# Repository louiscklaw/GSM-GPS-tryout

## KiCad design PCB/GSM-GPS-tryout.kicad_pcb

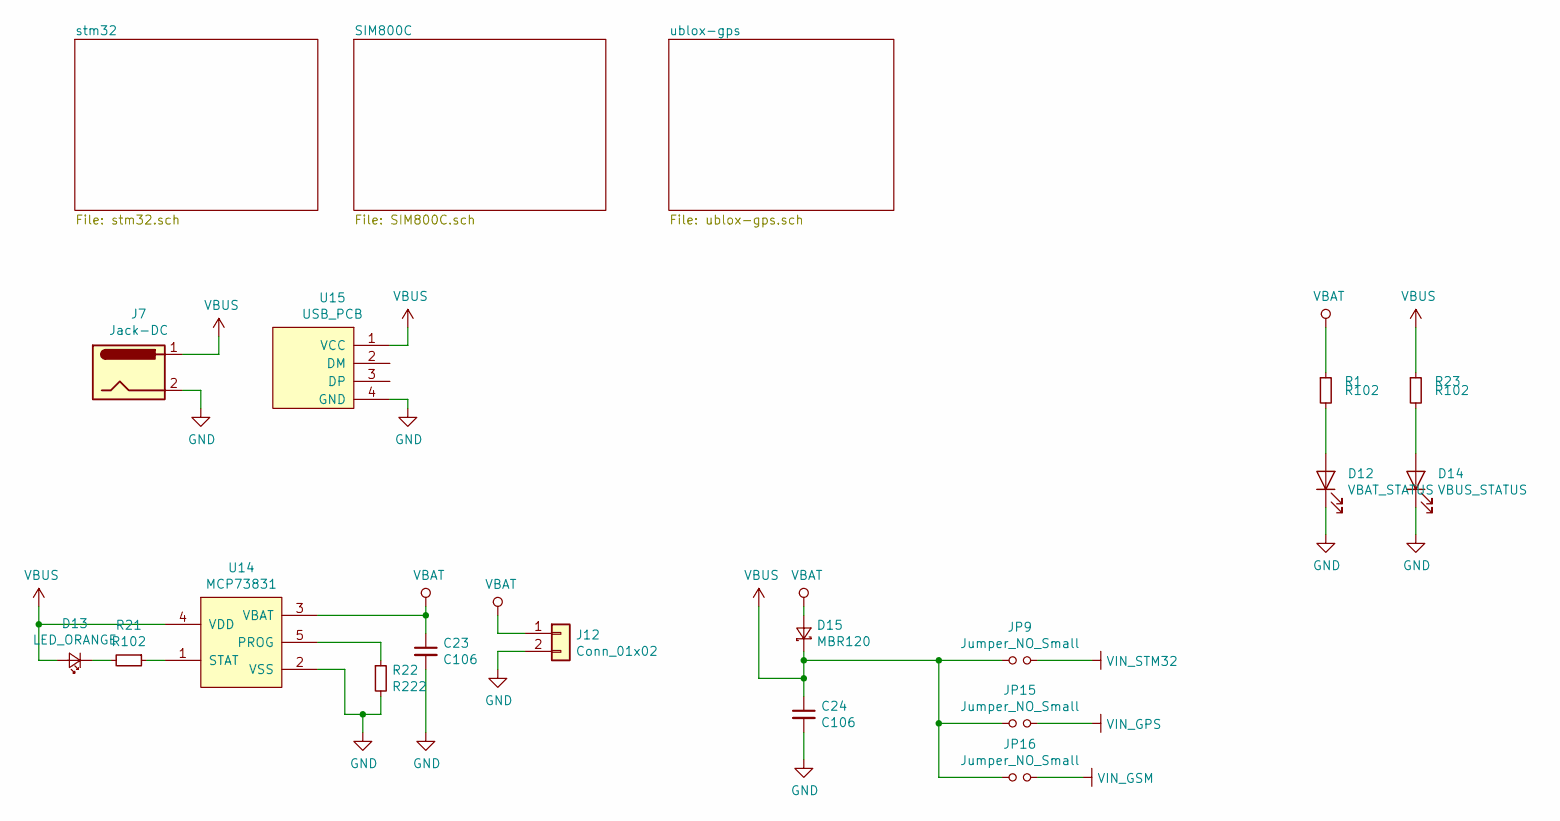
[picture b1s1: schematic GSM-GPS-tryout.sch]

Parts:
C23, C24: C106; C_0805_2012Metric_Pad1.15x1.40mm_HandSolder
D12: VBAT_STATUS; LED_0805_2012Metric_Pad1.15x1.40mm_HandSolder
D13: LED_ORANGE; LED_0805_2012Metric_Castellated
D14: VBUS_STATUS; LED_0805_2012Metric_Pad1.15x1.40mm_HandSolder
D15: MBR120; D_SOD-123F
J7: Jack-DC; CUI-PJ-102A_dc-barrel-jack
J12: Conn_01x02; PinHeader_1x02_P2.54mm_Vertical
JP9, JP15, JP16: Jumper_NO_Small; SolderJumper-2_P1.3mm_Open_TrianglePad1.0x1.5mm
R1, R21, R23: R102; R_0805_2012Metric_Pad1.15x1.40mm_HandSolder
R22: R222; R_0805_2012Metric_Pad1.15x1.40mm_HandSolder
U14: MCP73831; SOT-23-5_HandSoldering
U15: USB_PCB; usb-PCB

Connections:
GND: C23.2, C24.2, D12.1 (K), D14.1 (K), J7.2, J12.2, R22.2, U14.2 (VSS), U15.4 (GND); also elsewhere on the board
unnamed: D12.2 (A), R1.2
unnamed: D13.1 (K), R21.2
unnamed: D14.2 (A), R23.2
unnamed: R21.1, U14.1 (STAT)
unnamed: R22.1, U14.5 (PROG)
VBAT: C23.1, D15.2 (A), J12.1, R1.1, U14.3 (VBAT)
VBUS: C24.1, D13.2 (A), D15.1 (K), J7.1, JP9.1, JP15.1, JP16.1, R23.1, U14.4 (VDD), U15.1 (VCC)
VIN_GPS: JP15.2; also elsewhere on the board
VIN_GSM: JP16.2; also elsewhere on the board
VIN_STM32: JP9.2; also elsewhere on the board

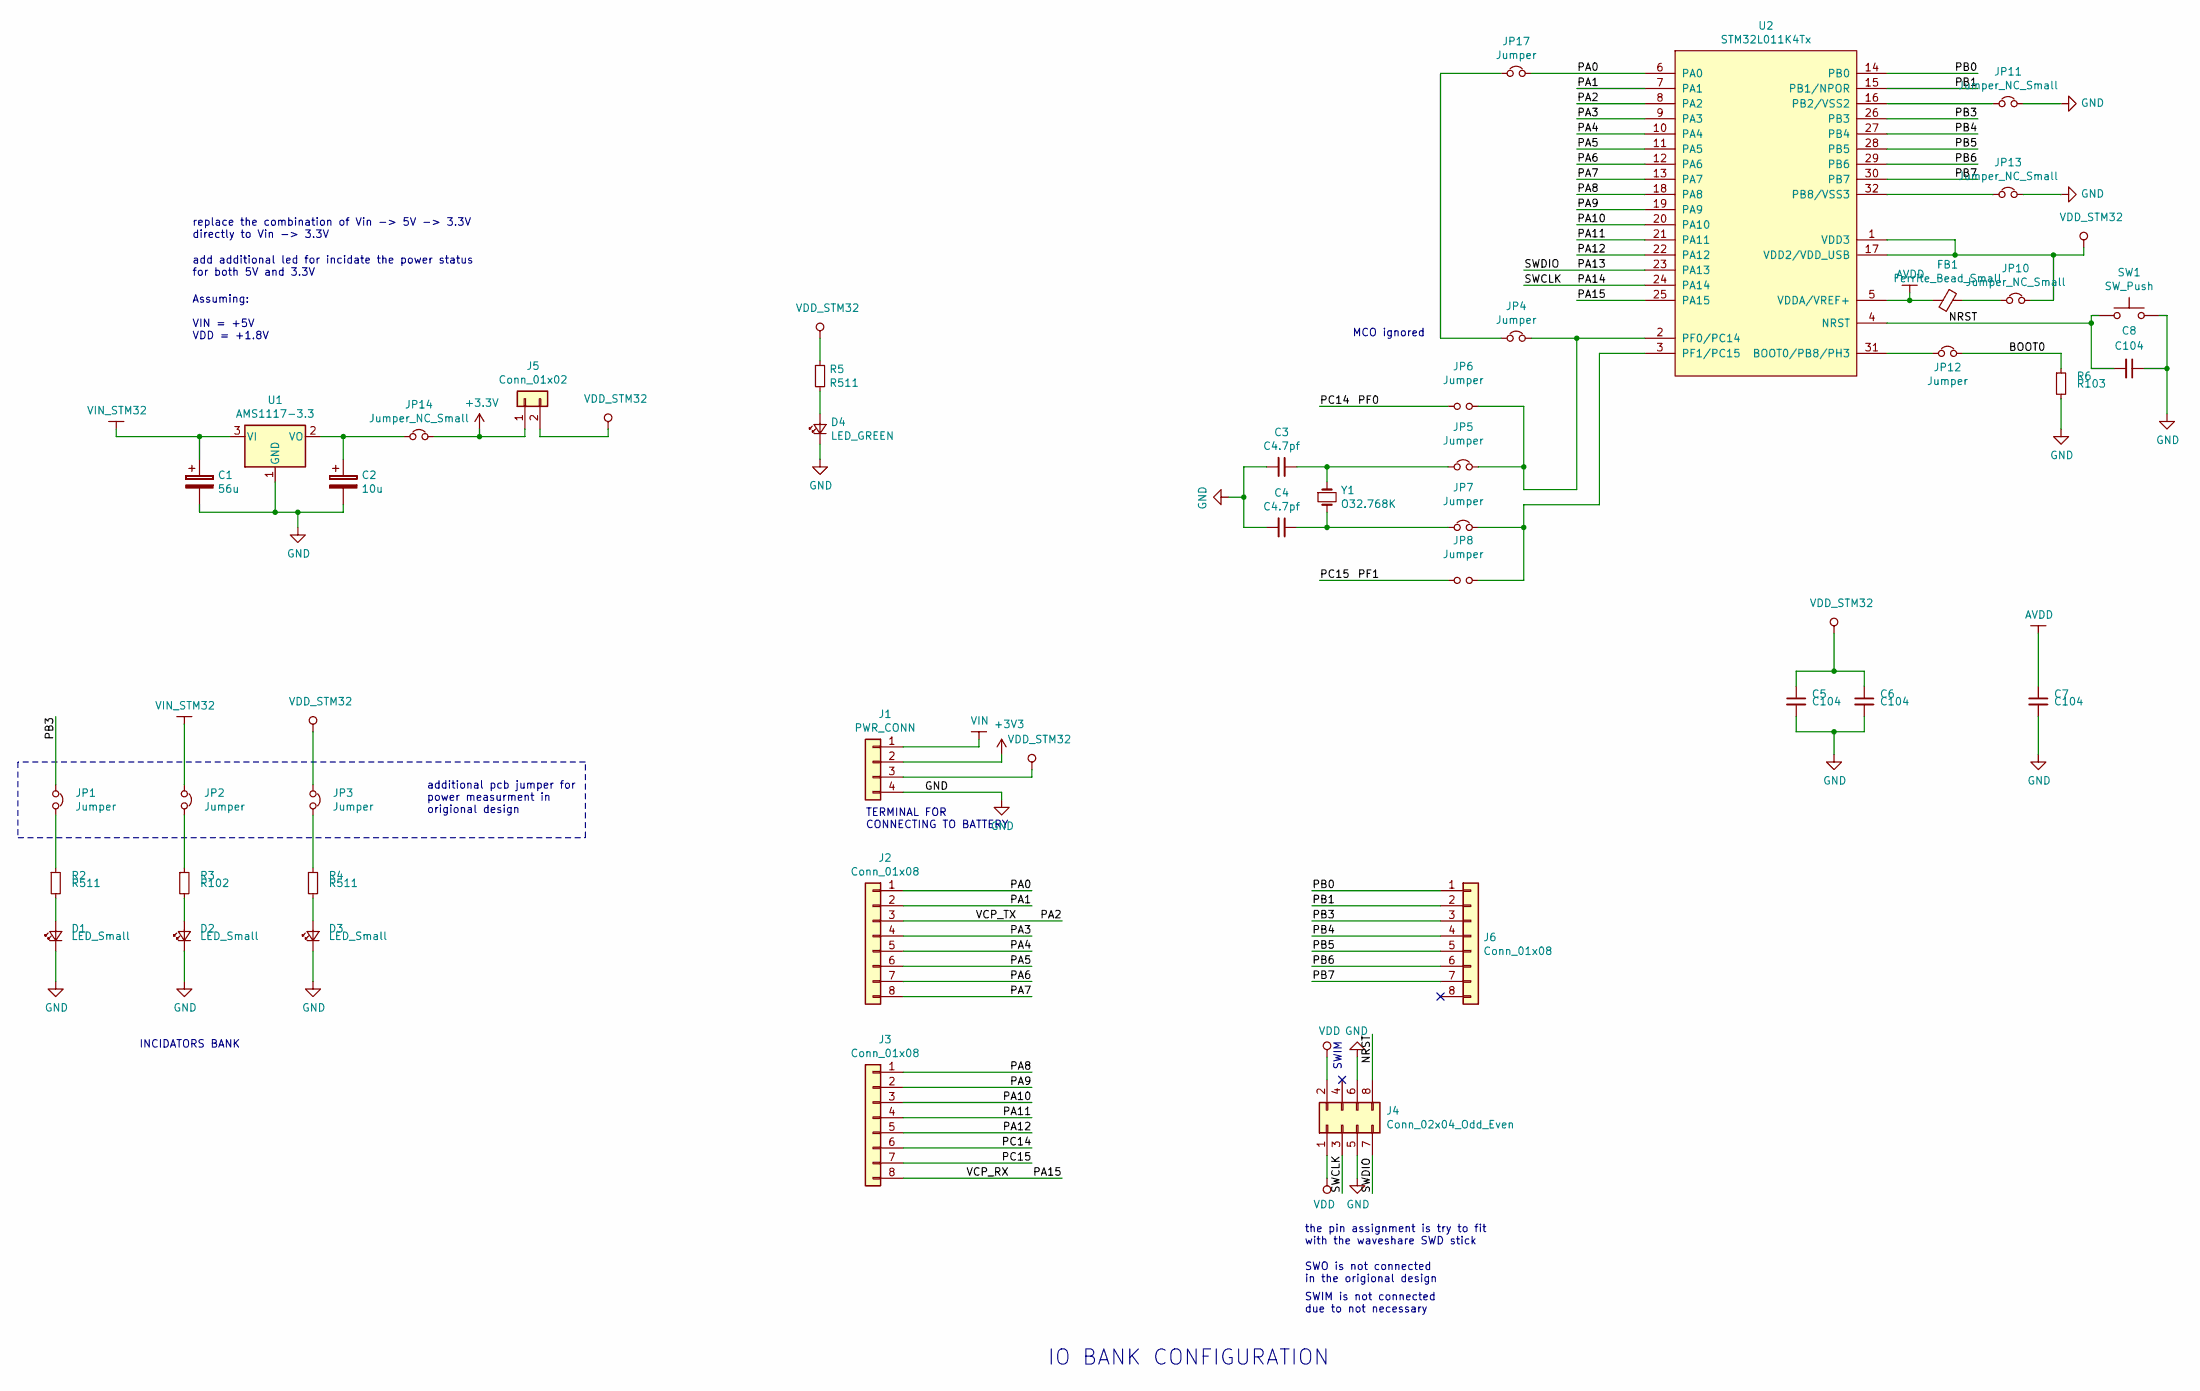
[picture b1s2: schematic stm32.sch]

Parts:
C1: 56u; CP_Elec_3x5.4
C2: 10u; CP_Elec_3x5.4
C3, C4: C4.7pf; C_0805_2012Metric_Pad1.15x1.40mm_HandSolder
C5, C6, C7, C8: C104; C_0805_2012Metric_Pad1.15x1.40mm_HandSolder
D1, D2, D3: LED_Small; LED_0805_2012Metric_Castellated
D4: LED_GREEN; LED_0805_2012Metric_Castellated
FB1: Ferrite_Bead_Small; inductor_smd_0805
J1: PWR_CONN; PinHeader_1x04_P2.54mm_Vertical
J2, J3, J6: Conn_01x08; PinHeader_1x08_P2.54mm_Vertical
J4: Conn_02x04_Odd_Even; PinHeader_2x04_P2.54mm_Vertical
J5: Conn_01x02; PinHeader_1x02_P2.54mm_Vertical
JP1, JP2, JP3, JP4, JP5, JP7, JP12, JP17: Jumper; SolderJumper-2_P1.3mm_Bridged_Pad1.0x1.5mm
JP6, JP8: Jumper; SolderJumper-2_P1.3mm_Open_TrianglePad1.0x1.5mm
JP10, JP11, JP13, JP14: Jumper_NC_Small; SolderJumper-2_P1.3mm_Bridged_Pad1.0x1.5mm
R2, R4, R5: R511; R_0805_2012Metric_Pad1.15x1.40mm_HandSolder
R3: R102; R_0805_2012Metric_Pad1.15x1.40mm_HandSolder
R6: R103; R_0805_2012Metric_Pad1.15x1.40mm_HandSolder
SW1: SW_Push; PCB_PUSH
U1: AMS1117-3.3; SOT-223-3_TabPin2
U2: STM32L011K4Tx; LQFP-32_7x7mm_P0.8mm
Y1: O32.768K; Crystal_C38-LF_D3.0mm_L8.0mm_Vertical

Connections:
/stm32/BOOT0: JP12.2, R6.1
/stm32/NRST: C8.2, J4.8, SW1.1, U2.4 (NRST)
/stm32/PA0: J2.1, JP17.2, U2.6 (PA0)
/stm32/PA1: J2.2, U2.7 (PA1)
/stm32/PA2: J2.3, U2.8 (PA2)
/stm32/PA3: J2.4, U2.9 (PA3)
/stm32/PA4: J2.5, U2.10 (PA4)
/stm32/PA5: J2.6, U2.11 (PA5)
/stm32/PA6: J2.7, U2.12 (PA6)
/stm32/PA7: J2.8, U2.13 (PA7)
/stm32/PA8: J3.1, U2.18 (PA8)
/stm32/PA9: J3.2, U2.19 (PA9)
/stm32/PA10: J3.3, U2.20 (PA10)
/stm32/PA11: J3.4, U2.21 (PA11)
/stm32/PA12: J3.5, U2.22 (PA12)
/stm32/PA13: J4.7, U2.23 (PA13)
/stm32/PA14: J4.3, U2.24 (PA14)
/stm32/PA15: J3.8, U2.25 (PA15)
/stm32/PB0: J6.1, U2.14 (PB0)
/stm32/PB1: J6.2, U2.15 (PB1/NPOR)
/stm32/PB3: J6.3, JP1.1, U2.26 (PB3)
/stm32/PB4: J6.4, U2.27 (PB4)
/stm32/PB5: J6.5, U2.28 (PB5)
/stm32/PB6: J6.6, U2.29 (PB6)
/stm32/PB7: J6.7, U2.30 (PB7)
/stm32/PC14: J3.6, JP6.1
/stm32/PC15: J3.7, JP8.1
AVDD: C7.1, FB1.2, U2.5 (VDDA/VREF+)
GND: C1.2, C2.2, C3.2, C4.2, C5.2, C6.2, C7.2, C8.1, D1.1 (K), D2.1 (K), D3.1 (K), D4.1 (K), J1.4, J4.5, J4.6, JP11.2, JP13.2, R6.2, SW1.2, U1.1 (GND); also elsewhere on the board
unnamed: C2.1, JP14.1, U1.2 (VO)
unnamed: C3.1, JP5.1, Y1.1
unnamed: C4.1, JP7.1, Y1.2
unnamed: D1.2 (A), R2.2
unnamed: D2.2 (A), R3.2
unnamed: D3.2 (A), R4.2
unnamed: D4.2 (A), R5.2
unnamed: FB1.1, JP10.1
unnamed: JP1.2, R2.1
unnamed: JP2.2, R3.1
unnamed: JP3.2, R4.1
unnamed: JP4.2, JP5.2, JP6.2, U2.2 (PF0/PC14)
unnamed: JP7.2, JP8.2, U2.3 (PF1/PC15)
unnamed: JP11.1, U2.16 (PB2/VSS2)
unnamed: JP12.1, U2.31 (BOOT0/PB8/PH3)
unnamed: JP13.1, U2.32 (PB8/VSS3)
unnamed: JP4.1, JP17.1
VDD: J4.1, J4.2
VDD_STM32: C5.1, C6.1, J1.3, J5.2, JP3.1, JP10.2, R5.1, U2.1 (VDD3), U2.17 (VDD2/VDD_USB)
VIN: J1.1
VIN_STM32: C1.1, JP2.1, U1.3 (VI); also elsewhere on the board

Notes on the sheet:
replace the combination of Vin -> 5V -> 3.3V directly to Vin -> 3.3V
IO BANK CONFIGURATION
add additional led for incidate the power status for both 5V and 3.3V
INCIDATORS BANK
SWO is not connected in the origional design
the pin assignment is try to fit with the waveshare SWD stick
additional pcb jumper for power measurment in origional design
TERMINAL FOR CONNECTING TO BATTERY
SWIM is not connected due to not necessary
SWIM
MCO ignored
Assuming: VIN = +5V VDD = +1.8V

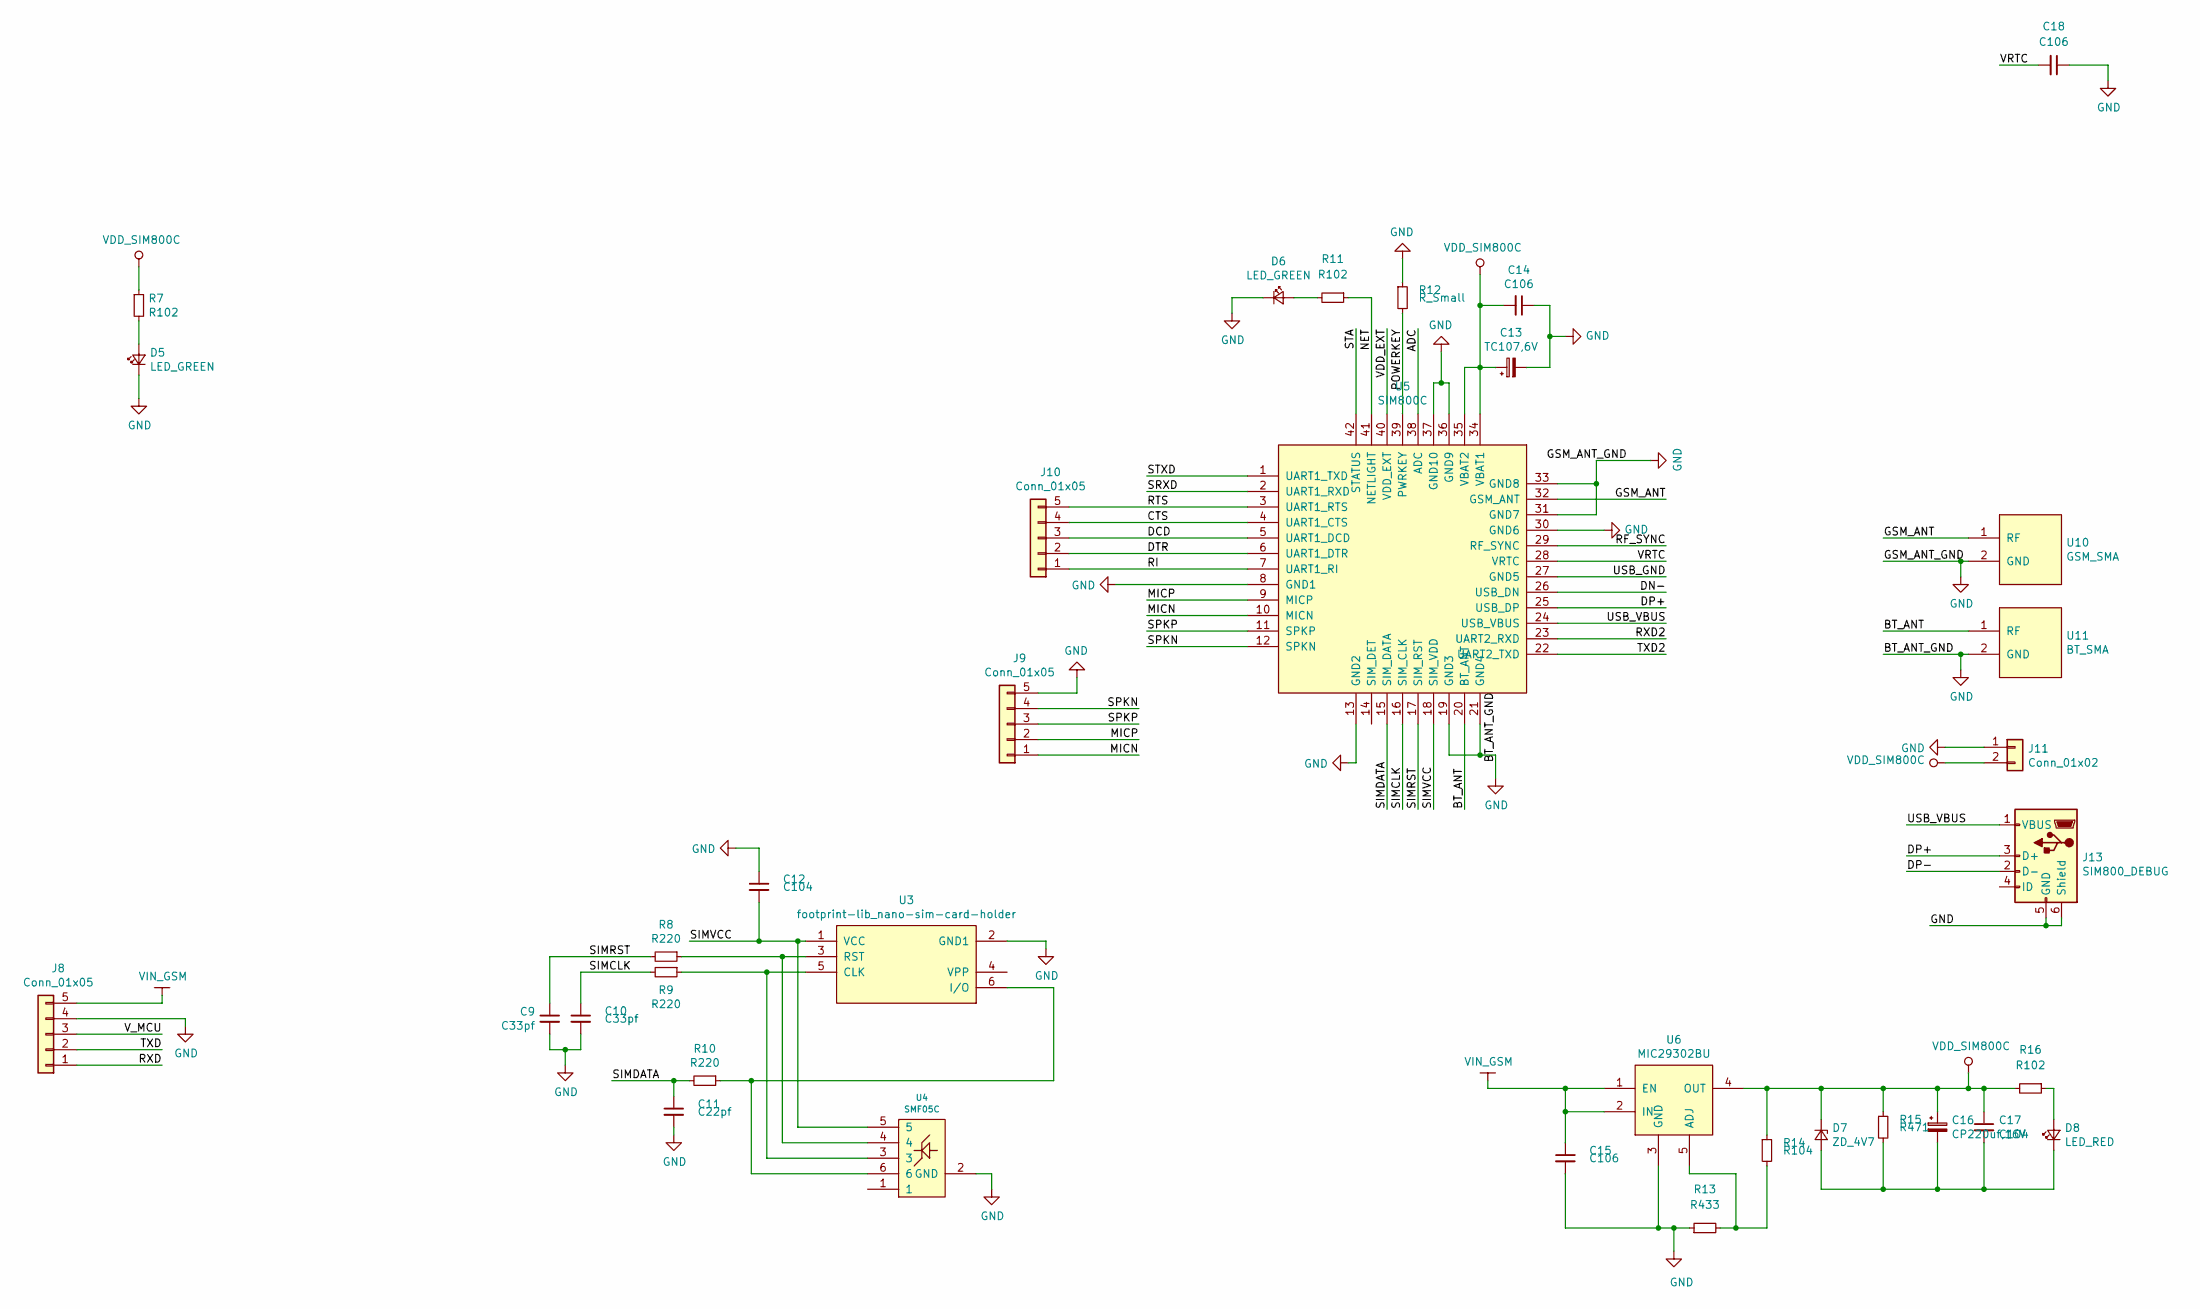
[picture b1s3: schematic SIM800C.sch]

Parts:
C9, C10: C33pf; C_0805_2012Metric_Pad1.15x1.40mm_HandSolder
C11: C22pf; C_0805_2012Metric_Pad1.15x1.40mm_HandSolder
C12: C104; C_0805_2012Metric_Pad1.15x1.40mm_HandSolder
C13: TC107,6V; CP_EIA-3216-12_Kemet-S_Pad1.58x1.35mm_HandSolder
C14, C15: C106; C_0805_2012Metric_Pad1.15x1.40mm_HandSolder
C16: CP220uf,16V; CP_Elec_6.3x7.7
C17: C104; C_0603_1608Metric_Pad1.05x0.95mm_HandSolder
C18: C106; C_0603_1608Metric_Pad1.05x0.95mm_HandSolder
D5, D6: LED_GREEN; LED_0805_2012Metric_Castellated
D7: ZD_4V7; D_1206_3216Metric_Pad1.42x1.75mm_HandSolder
D8: LED_RED; LED_0805_2012Metric_Castellated
J8, J9, J10: Conn_01x05; PinHeader_1x05_P2.54mm_Vertical
J11: Conn_01x02; PinHeader_1x02_P2.54mm_Vertical
J13: SIM800_DEBUG; conn_usb_B_micro_smd
R7, R11, R16: R102; R_0805_2012Metric_Pad1.15x1.40mm_HandSolder
R8, R9, R10: R220; R_0805_2012Metric_Pad1.15x1.40mm_HandSolder
R12: R_Small; R_0805_2012Metric_Pad1.15x1.40mm_HandSolder
R13: R433; R_0805_2012Metric_Pad1.15x1.40mm_HandSolder
R14: R104; R_0805_2012Metric_Pad1.15x1.40mm_HandSolder
R15: R471; R_0805_2012Metric_Pad1.15x1.40mm_HandSolder
U3: footprint-lib_nano-sim-card-holder; nano-sim-card-holder
U4: SMF05C; SOT-363_SC-70-6_Handsoldering
U5: SIM800C; LCC110P1570X1760X250-42N
U6: MIC29302BU; TO-263-5_TabPin3
U10: GSM_SMA; sma_straight_32k101-400l5
U11: BT_SMA; sma_straight_32k101-400l5

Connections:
/SIM800C/ADC: U5.38 (ADC)
/SIM800C/BT_ANT: U5.20 (BT_ANT), U11.1 (RF)
/SIM800C/CTS: J10.4, U5.4 (UART1_CTS)
/SIM800C/DCD: J10.3, U5.5 (UART1_DCD)
/SIM800C/DN-: U5.26 (USB_DN)
/SIM800C/DP+: J13.3 (D+), U5.25 (USB_DP)
/SIM800C/DP-: J13.2 (D-)
/SIM800C/DTR: J10.2, U5.6 (UART1_DTR)
/SIM800C/GSM_ANT: U5.32 (GSM_ANT), U10.1 (RF)
/SIM800C/MICN: J9.1, U5.10 (MICN)
/SIM800C/MICP: J9.2, U5.9 (MICP)
/SIM800C/NET: R11.1, U5.41 (NETLIGHT)
/SIM800C/POWERKEY: R12.2, U5.39 (PWRKEY)
/SIM800C/RF_SYNC: U5.29 (RF_SYNC)
/SIM800C/RI: J10.1, U5.7 (UART1_RI)
/SIM800C/RTS: J10.5, U5.3 (UART1_RTS)
/SIM800C/RXD: J8.1
/SIM800C/RXD2: U5.23 (UART2_RXD)
/SIM800C/SIMCLK: C10.1, R9.2, U5.16 (SIM_CLK)
/SIM800C/SIMDATA: C11.1, R10.2, U5.15 (SIM_DATA)
/SIM800C/SIMRST: C9.1, R8.2, U5.17 (SIM_RST)
/SIM800C/SIMVCC: C12.2, U3.1 (VCC), U4.5, U5.18 (SIM_VDD)
/SIM800C/SPKN: J9.4, U5.12 (SPKN)
/SIM800C/SPKP: J9.3, U5.11 (SPKP)
/SIM800C/SRXD: U5.2 (UART1_RXD)
/SIM800C/STA: U5.42 (STATUS)
/SIM800C/STXD: U5.1 (UART1_TXD)
/SIM800C/TXD: J8.2
/SIM800C/TXD2: U5.22 (UART2_TXD)
/SIM800C/USB_GND: U5.27 (GND5)
/SIM800C/USB_VBUS: J13.1 (VBUS), U5.24 (USB_VBUS)
/SIM800C/VDD_EXT: U5.40 (VDD_EXT)
/SIM800C/VRTC: C18.2, U5.28 (VRTC)
/SIM800C/V_MCU: J8.3
GND: C9.2, C10.2, C11.2, C12.1, C13.2, C14.1, C15.2, C18.1, D5.1 (K), D6.1 (K), J8.4, J9.5, J11.1, J13.5 (GND), J13.6 (Shield), R12.1, R13.1, U3.2 (GND1), U4.2 (GND), U5.8 (GND1), U5.13 (GND2), U5.19 (GND3), U5.21 (GND4), U5.30 (GND6), U5.31 (GND7), U5.33 (GND8), U5.36 (GND9), U5.37 (GND10), U6.3 (GND), U10.2 (GND), U11.2 (GND); also elsewhere on the board
unnamed: C16.2, C17.2, D7.2 (A), D8.1 (K), R15.2
unnamed: D5.2 (A), R7.2
unnamed: D6.2 (A), R11.2
unnamed: D8.2 (A), R16.1
unnamed: R8.1, U3.3 (RST), U4.4
unnamed: R9.1, U3.5 (CLK), U4.3
unnamed: R10.1, U3.6 (I/O), U4.6
unnamed: R13.2, R14.2, U6.5 (ADJ)
VDD_SIM800C: C13.1, C14.2, C16.1, C17.1, D7.1 (K), J11.2, R7.1, R14.1, R15.1, R16.2, U5.34 (VBAT1), U5.35 (VBAT2), U6.4 (OUT)
VIN_GSM: C15.1, J8.5, U6.1 (EN), U6.2 (IN); also elsewhere on the board

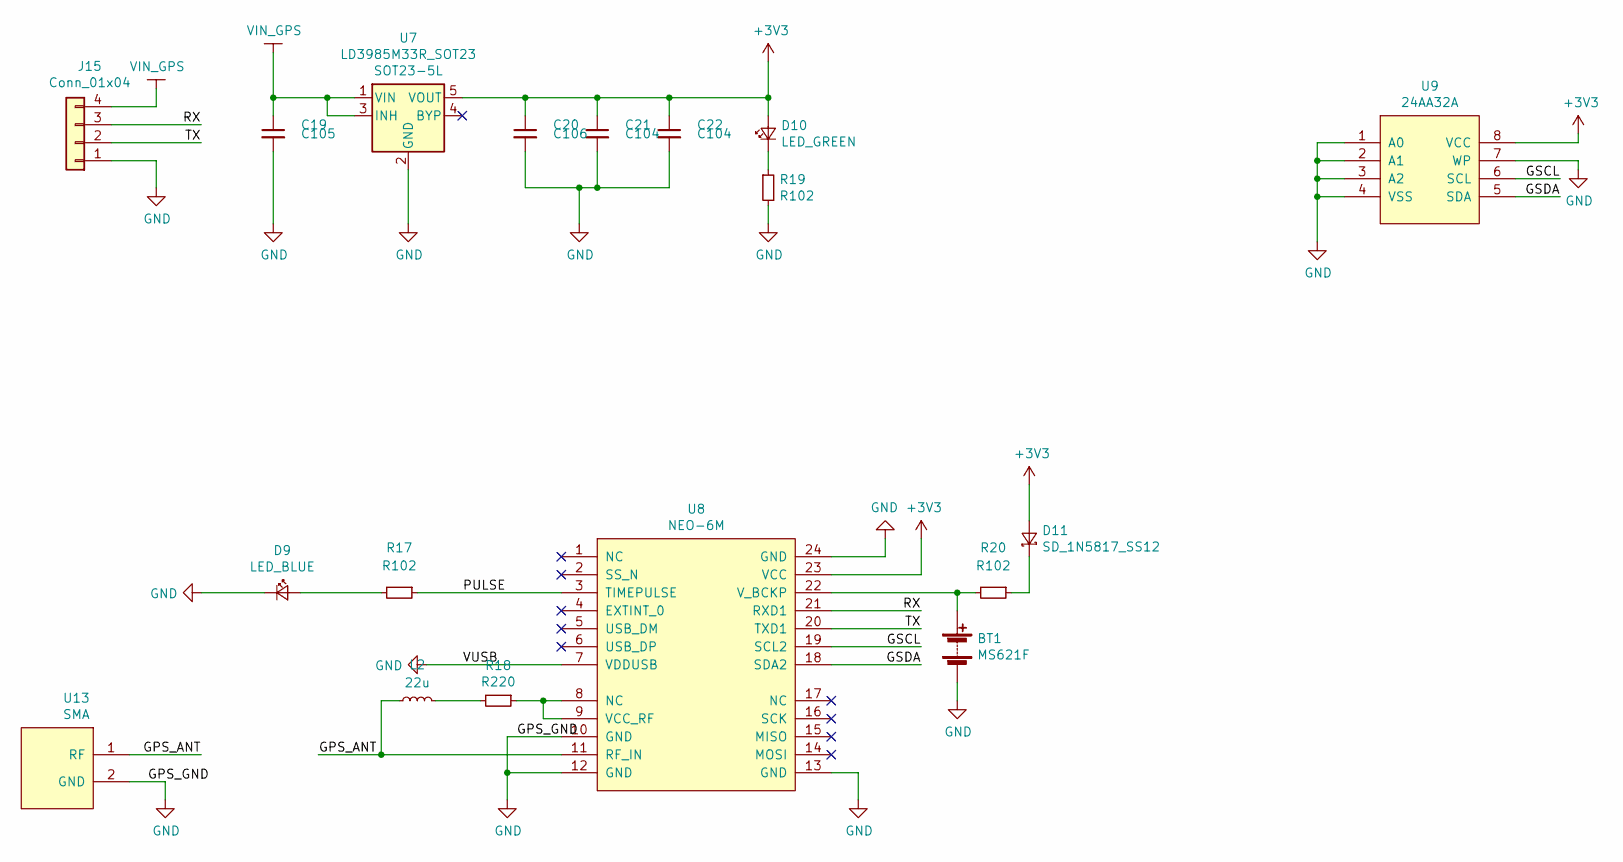
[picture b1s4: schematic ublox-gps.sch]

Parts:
BT1: MS621F; BatteryHolder_Seiko_MS621F
C19: C105; C_0603_1608Metric_Pad1.05x0.95mm_HandSolder
C20: C106; C_0603_1608Metric_Pad1.05x0.95mm_HandSolder
C21, C22: C104; C_0603_1608Metric_Pad1.05x0.95mm_HandSolder
D9: LED_BLUE; LED_0805_2012Metric_Castellated
D10: LED_GREEN; LED_0805_2012Metric_Castellated
D11: SD_1N5817_SS12; D_1206_3216Metric_Pad1.42x1.75mm_HandSolder
J15: Conn_01x04; PinHeader_1x04_P2.54mm_Vertical
L2: 22u; inductor_smd_0805
R17, R19, R20: R102; R_0805_2012Metric_Pad1.15x1.40mm_HandSolder
R18: R220; R_0805_2012Metric_Pad1.15x1.40mm_HandSolder
U7: LD3985M33R_SOT23; SOT-23-5
U8: NEO-6M; ublox_NEO
U9: 24AA32A; SOT-23-8_Handsoldering
U13: SMA; sma_straight_32k101-400l5

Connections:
/ublox-gps/GPS_ANT: L2.1, U8.11 (RF_IN), U13.1 (RF)
/ublox-gps/GSCL: U8.19 (SCL2), U9.6 (SCL)
/ublox-gps/GSDA: U8.18 (SDA2), U9.5 (SDA)
/ublox-gps/PULSE: R17.1, U8.3 (TIMEPULSE)
/ublox-gps/RX: J15.3, U8.21 (RXD1)
/ublox-gps/TX: J15.2, U8.20 (TXD1)
GND: BT1.2 (-), C19.2, C20.2, C21.2, C22.2, D9.1 (K), J15.1, R19.2, U7.2 (GND), U8.7 (VDDUSB), U8.10 (GND), U8.12 (GND), U8.13 (GND), U8.24 (GND), U9.1 (A0), U9.2 (A1), U9.3 (A2), U9.4 (VSS), U9.7 (WP), U13.2 (GND); also elsewhere on the board
unnamed: BT1.1 (+), R20.2, U8.22 (V_BCKP)
unnamed: D9.2 (A), R17.2
unnamed: D10.1 (K), R19.1
unnamed: D11.1 (K), R20.1
unnamed: L2.2, R18.2
unnamed: R18.1, U8.8 (NC), U8.9 (VCC_RF)
VIN_GPS: C19.1, J15.4, U7.1 (VIN), U7.3 (INH); also elsewhere on the board

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
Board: 2 copper layers, 112 parts (0 on the bottom side), 100 nets, no tracks yet.

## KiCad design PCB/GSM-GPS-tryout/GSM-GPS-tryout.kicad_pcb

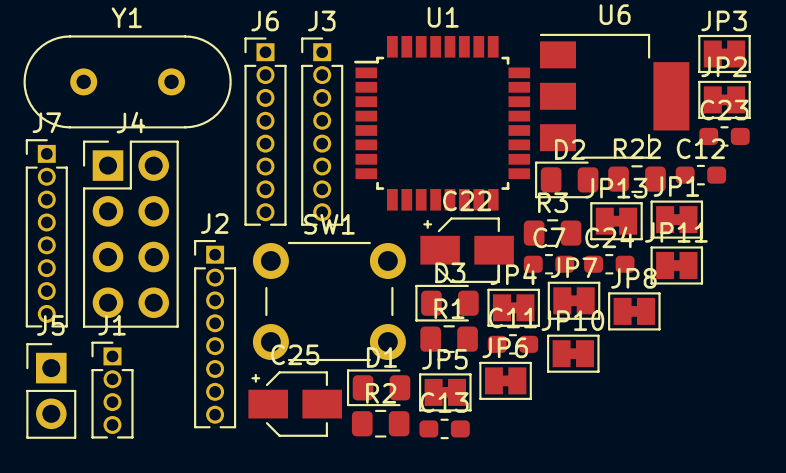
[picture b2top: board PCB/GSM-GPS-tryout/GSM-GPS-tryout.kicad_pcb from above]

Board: 2 copper layers, 37 parts (0 on the bottom side), 43 nets, no tracks yet.

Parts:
C7, C11, C23, C24: 100n; C_0603_1608Metric_Pad1.05x0.95mm_HandSolder
C12, C13: 4.3p; C_0603_1608Metric_Pad1.05x0.95mm_HandSolder
C22, C25: 10u; CP_Elec_3x5.4
D1: LED; LED_0805_2012Metric_Pad1.15x1.40mm_HandSolder
D2, D3: RED; LED_0805_2012Metric_Pad1.15x1.40mm_HandSolder
J1: Conn_01x04; PinHeader_1x04_P1.27mm_Vertical
J2, J3, J6, J7: Conn_01x08; PinHeader_1x08_P1.27mm_Vertical
J4: Conn_02x04_Row_Letter_First; PinHeader_2x04_P2.54mm_Vertical
J5: Conn_01x02; PinHeader_1x02_P2.54mm_Vertical
JP1, JP2, JP3, JP4, JP5, JP6, JP7, JP8, JP10, JP11, JP13: Jumper; SolderJumper-2_P1.3mm_Bridged_Pad1.0x1.5mm
R1, R2, R22: 510; R_0805_2012Metric_Pad1.15x1.40mm_HandSolder
R3: R; R_0805_2012Metric_Pad1.15x1.40mm_HandSolder
SW1: SW_SPST; SW_PUSH_6mm_H4.3mm
U1: STM32L011K4Tx; LQFP-32_7x7mm_P0.8mm
U6: AMS1117-1.8; SOT-223-3_TabPin2
Y1: 32.768K; Crystal_HC49-4H_Vertical

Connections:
+3V3: C7.1, C23.1, J1.2, J5.2, J7.2, JP3.1, JP10.1, U1.1, U1.17
+5V: C22.1, J1.1, J7.1, JP2.1, U6.3
/AVDD: C24.1, U1.5
/BOOT0: JP4.1, U1.31
/NRST: C11.1, SW1.2, U1.4
/PA0: J2.1, U1.6
/PA1: J2.2, U1.7
/PA2: J2.3, U1.8
/PA3: J2.4, U1.9
/PA4: J2.5, U1.10
/PA5: J2.6, U1.11
/PA6: J2.7, U1.12
/PA7: J2.8, U1.13
/PA8: J3.1, U1.18
/PA9: J3.2, U1.19
/PA10: J3.3, U1.20
/PA11: J3.4, U1.21
/PA12: J3.5, U1.22
/PA15: J3.8, U1.25
/PB0: J6.1, U1.14
/PB1: J6.2, U1.15
/PB3: J6.3, JP1.1, U1.26
/PB4: J6.4, U1.27
/PB5: J6.5, U1.28
/PB6: J6.6, U1.29
/PB7: J6.7, U1.30
/PC14: J7.7, JP6.1
/PC15: J7.8, JP8.1
GND: C7.2, C11.2, C12.2, C13.2, C22.2, C23.2, C24.2, C25.2, D1.1, D2.1, D3.1, J1.4, J7.3, JP11.1, JP13.1, R3.2, SW1.1, U6.1
unnamed: C12.1, JP5.1, Y1.1
unnamed: C13.1, JP7.1, Y1.2
unnamed: C25.1, J5.1, U6.2
unnamed: D1.2, R1.2
unnamed: D2.2, R22.2
unnamed: D3.2, R2.2
unnamed: JP1.2, R1.1
unnamed: JP2.2, R22.1
unnamed: JP3.2, R2.1
unnamed: JP4.2, R3.1
unnamed: JP5.2, JP6.2, U1.2
unnamed: JP7.2, JP8.2, U1.3
unnamed: JP11.2, U1.16
unnamed: JP13.2, U1.32

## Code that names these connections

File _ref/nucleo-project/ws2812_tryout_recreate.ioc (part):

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Mcu.Name=STM32L011K(3-4)Tx
Mcu.Package=LQFP32
Mcu.UserName=STM32L011K4Tx
PA0-CK_IN.Mode=SYS_WakeUp0
PA0-CK_IN.Signal=SYS_WKUP1
PA13.GPIOParameters=GPIO_Label
PA13.GPIO_Label=TMS
PA13.Mode=Serial_Wire
PA13.Signal=SYS_SWDIO
PA14.GPIOParameters=GPIO_Label
PA14.GPIO_Label=TCK
PA14.Mode=Serial_Wire
PA14.Signal=SYS_SWCLK
PA15.GPIOParameters=GPIO_Label
PA15.GPIO_Label=VCP_RX
PA15.Mode=Asynchronous
PA15.Signal=USART2_RX
PA2.GPIOParameters=GPIO_Label
PA2.GPIO_Label=VCP_TX
PA2.Mode=Asynchronous
PA2.Signal=USART2_TX
PA3.Mode=Asynchronous
PA3.Signal=LPUART1_RX
PA4.Mode=Asynchronous
PA4.Signal=LPUART1_TX
PB3.GPIOParameters=GPIO_Label
PB3.GPIO_Label=LD3 [Green]
PB3.Signal=GPIO_Output
PC14-OSC32_IN.Mode=LSE-External-Oscillator
PC14-OSC32_IN.Signal=RCC_OSC32_IN
PC15-OSC32_OUT.Mode=LSE-External-Oscillator
PC15-OSC32_OUT.Signal=RCC_OSC32_OUT
RCC.HSE_VALUE=8000000
RCC.SYSCLKFreq_VALUE=32000000
RCC.SYSCLKSource=RCC_SYSCLKSOURCE_PLLCLK
board=NUCLEO-L011K4
boardIOC=true

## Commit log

2018-10-04 init commit,
2018-10-04 update,
2018-10-04 update SIM800c-modules,
2018-10-04 update GPS,
2018-10-13 test
2018-10-15 updte
2020-05-05 ci: init travis build config,
2020-05-05 ci: init travis token,
